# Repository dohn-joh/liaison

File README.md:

# Liaison
`Liaison` is a wireless 36-key split keyboard that leverages custom keycaps, splay, and tenting for ergonomics.

**Video showcase**:  
[Fit and layout](https://vimeo.com/1022366207)  
[Typing test](https://vimeo.com/1022366241)

***

# Components

## Case and Tenting Legs
[Here](case) you can find models for the case and magsafe tenting legs.  
Print 1 of each of the following:
* [top left](case/case_top_left.step)
* [top right](case/case_top_right.step)
* [bottom left](case/case_bottom_left.step)
* [bottom right](case/case_bottom_right.step)

[Tenting legs](case/magsafe_tenting_leg) (optional)  
[Dongle case](https://github.com/dohn-joh/dongle-zmk) (optional)

## Required Parts
|Part|Quantity|Link|
|-|:-:|-|
|Microcontroller: Xiao nRF52840|1|https://www.seeedstudio.com/Seeed-XIAO-BLE-nRF52840-p-5201.html|
|Battery: 301230 with molex pico ezmate connector|1|Select L0040. https://www.aliexpress.us/item/3256802674181210.html|
|Battery connector: molex pico ezmate 1x02|1|Select 2P. https://www.aliexpress.us/item/3256805726980487.html|
|Power button: 1208YD|1|https://www.aliexpress.us/item/3256801267126259.html|
|Reset button: SKHLLCA010|1|https://www.aliexpress.us/item/3256805176534062.html|
|M2 heatset inserts (OD:3.2, Height: 2-3mm)|8|https://www.aliexpress.us/item/3256804856964661.html|
|Switches|36|Your choice of choc v1 or v2. Recommended: Lofree ghost, swap springs|
|Kailh Choc PG1350 Hot Swap Sockets|36|https://www.aliexpress.us/item/3256803687338432.html|
|Silicone sheet for feet|1|https://www.amazon.com/dp/B09NW63JLC|
|Keycaps|36|Your choice. Recommended: [low profile DES](https://github.com/dohn-joh/PseudoMakeMeKeyCapProfiles) + [lever keycaps](https://github.com/dohn-joh/keycaps)|

> [!NOTE]
> Keycap dimensions must be ≤17.85mm wide and ≤18mm deep. All standard choc keycaps will fit.

## Optional Parts for Tenting Legs and Magnetic USB
|Part|Quantity|Link|
|-|:-:|-|
|Magsafe puck: Vrig MG-01|2|https://www.aliexpress.us/item/3256804940825578.html|
|Magsafe plate|2|https://www.amazon.com/dp/B09B6XGTWL|
|1/4" thread screw ~9mm|2|There are cheaper sources out there, but here is a link: https://www.amazon.com/dp/B01MS60KSY|
|Magnetic USB connector/cable: Netdot Gen10|2|https://www.amazon.com/dp/B07MBD3FZD|

## Firmware
[Here](https://github.com/dohn-joh/liaison-zmk-module) you can find the liaison's ZMK module. The firmware is configured for dongle usage, however you may fork the repo if you prefer to not use a dongle.

# Build Guide

**1. Order the pcb and acquire the case**
* Download the [left](ergogen/output/pcbs/production/Left_v1.0.0.zip) and [right](ergogen/output/pcbs/production/Right_v1.0.0.zip) pcb zip files.
* Upload the zip files to your pcb manufacturer of choice, then place an order. I used jlcpcb.
* Acquire the case:
    * If you own a 3d printer: print the [case](README.md#case-and-tenting).
    * If you don't own a 3d printer: order the case prints using [these files](README.md#case-and-tenting).

**2. Order [parts](README.md#required-parts)**

**3. Flash and test the microcontrollers**
> [!IMPORTANT]
> **Flash your microcontrollers with firmware and test them before doing any soldering.** Once the microcontrollers are soldered, they will be nearly impossible to remove without the right tools.
* Flash the [firmware](https://github.com/dohn-joh/liaison-zmk-module).
* Test to make sure that the microcontrollers are working and not defective (defective units are rare, but it happens).

**4. Solder components to top face of pcb**
* Set your soldering iron to 350C.
* Solder the microcontrollers, diodes, [reset switch](https://github.com/GEIGEIGEIST/TOTEM/blob/main/docs/buildguide.md#reset-switches), power switch, and battery connector to the top face of the pcb.
* The battery connector can be tricky to solder. But once you get the hang of it, it's pretty easy. Here are some tips from Kim:
    > Apply flux on both the pcb pads and battery connector pins  
    Tin both corner pads with solder  
    Solder connector to the first corner by applying heat to the corner metal pin from above  
    Then do the same for the second corner  
    Apply more flux to connector pins and PCB pads  
    Apply solder to underside of soldering tip  
    Drag iron from side to side over the contacts until they are soldered. The solder will just jump to where it needs to go  
    Make sure to clean the flux thoroughly
* The power button needs to face downward. Trim the power switch legs to size before installing. Secure the power switch in place with kapton tape after soldering.

**5. Check your work**
* This step is optional, but I like to check my work before moving on to soldering the other side of the pcb.
* Make sure all diodes are oriented correctly. All lines or arrows should be pointing left.
* Set your multimeter to continuity mode.
* Check connections and look for bridging.
* Fix any solder joints as needed.

**6. Solder components to bottom face of pcb**
> [!IMPORTANT]
> Hotswap socket orientation matters. The sockets must align with the silkscreen or the bottom case will not fit.
* Solder the hotswap sockets to the bottom face of the pcb.
* Optional: check your work with a multimeter.

**7. Battery installation**
* Plug the battery into the connector.
* Use kapton tape to secure the battery within the silkscreen outline.

**8. Case assembly**
* With your soldering iron set to 300C, push heatset inserts into the 4 holes on the top case.
* Insert the pcb.
* Attach the bottom case and secure it in place with the M2 screws.
    * If the bottom case doesn't sit flush in the area around the reset switch, then you may need to trim the reset switch legs.
* Cut silicone sheet to size and adhere to the corners of the bottom case.
* Insert the switches and keycaps.

**9. (Optional) Tenting assembly**
* Screw the magsafe pucks onto the tenting legs.
* Adhere magsafe plate to bottom case.
* Cut silicone sheet to size and adhere to bottom of tenting legs.

***

# Photos

***

## Thanks
These people and many more helped make this keyboard possible. Yall are legends.
```
MrZealot
Pseudoku
petejohanson
caksoylar(bravekarma)
jcmkk3
ceoloide
infused-kim
Flatfootfox
sadekbaroudi
zzeneg
joelspadin
wolfwood
claussen
Geist
rmwphd(atinyzubat)
fish
Araxia
honorless
elkepenin
reeves
```

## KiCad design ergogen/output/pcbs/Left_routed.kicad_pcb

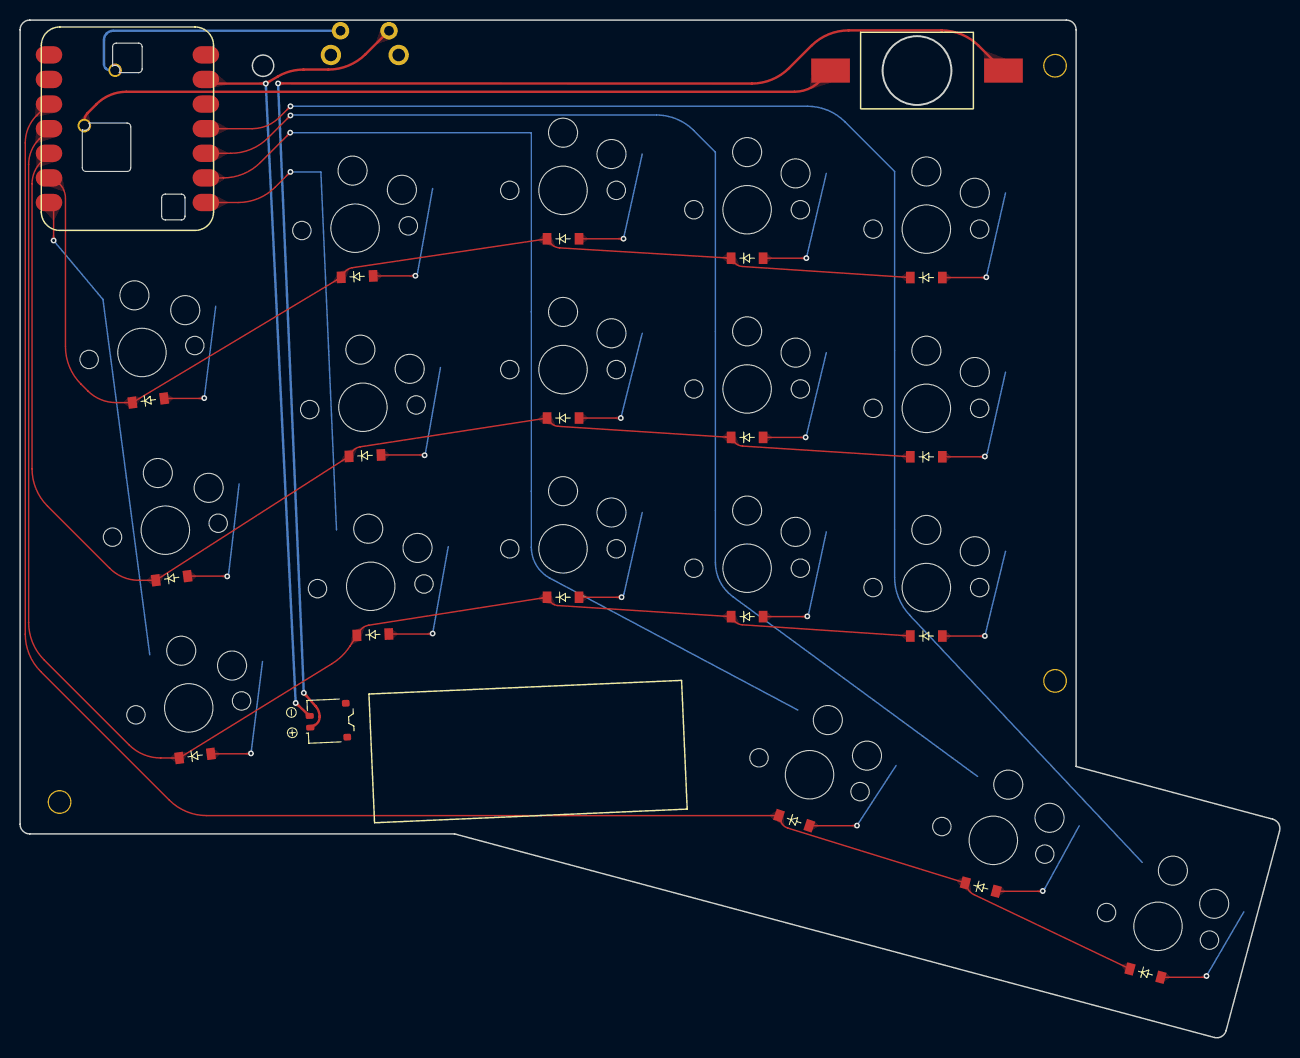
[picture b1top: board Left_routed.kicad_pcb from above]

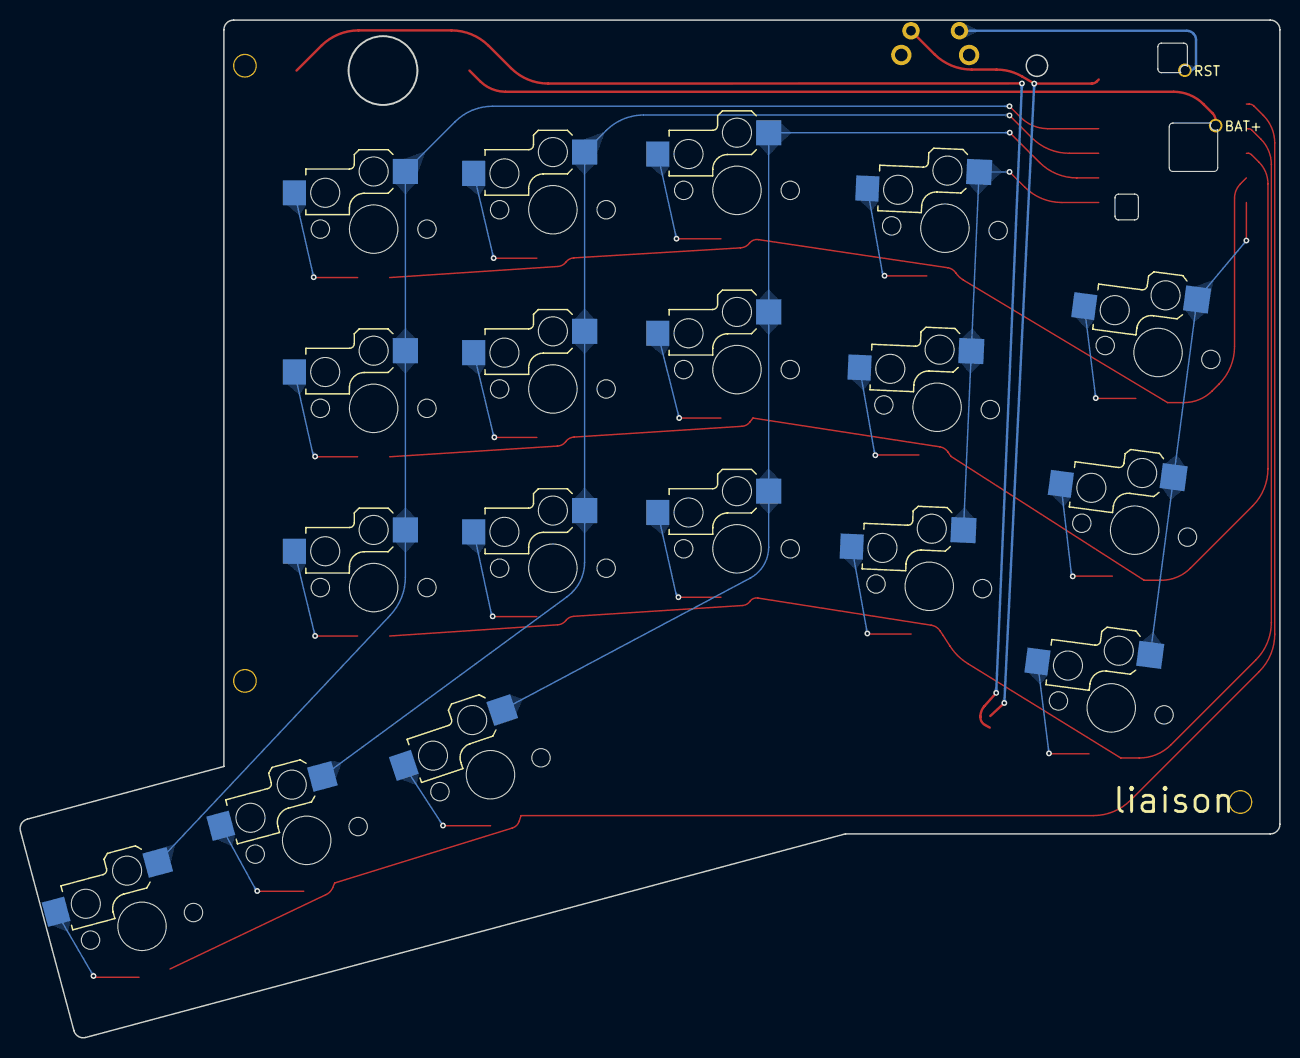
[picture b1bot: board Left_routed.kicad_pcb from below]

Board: 2 copper layers, 130.0 x 105.0 mm, 44 parts (18 on the bottom side), 31 nets.

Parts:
CONN1: conn_molex_pico_ezmate_1x02
D1, D2, D3, D4, D5, D6, D7, D8, D9, D10, D11, D12, D13, D14, D15, D16, D17, D18: ComboDiode
H1, H2, H3: mounting_hole
ICON1: icon_bat
MCU1: xiao_smd_xl_cutout_minimal
S1, S2, S3, S4, S5, S6, S7, S8, S9, S10, S11, S12, S13, S14, S15, S16, S17, S18: switch_choc_v1_v2
S19: SKHLLCA010
SW1: 1208YD

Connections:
BAT: MCU1.19, SW1.1
BAT_CONN: CONN1.1, SW1.2
C0: MCU1.7, S1.1, S2.1, S3.1
C1: MCU1.8, S4.1, S5.1, S6.1
C2: MCU1.9, S7.1, S8.1, S9.1, S16.1
C3: MCU1.10, S10.1, S11.1, S12.1, S17.1
C4: MCU1.11, S13.1, S14.1, S15.1, S18.1
GND: CONN1.2, MCU1.13, S19.2
R0: D3.1, D6.1, D9.1, D12.1, D15.1, MCU1.6
R1: D2.1, D5.1, D8.1, D11.1, D14.1, MCU1.5
R2: D1.1, D4.1, D7.1, D10.1, D13.1, MCU1.4
R3: D16.1, D17.1, D18.1, MCU1.3
RST: MCU1.17, S19.1
base_cluster: D17.2, S17.2
extension_cluster: D18.2, S18.2
flexion_cluster: D16.2, S16.2
index_bottom: D10.2, S10.2
index_home: D11.2, S11.2
index_top: D12.2, S12.2
inner_bottom: D13.2, S13.2
inner_home: D14.2, S14.2
inner_top: D15.2, S15.2
middle_bottom: D7.2, S7.2
middle_home: D8.2, S8.2
middle_top: D9.2, S9.2
pinky_bottom: D1.2, S1.2
pinky_home: D2.2, S2.2
pinky_top: D3.2, S3.2
ring_bottom: D4.2, S4.2
ring_home: D5.2, S5.2
ring_top: D6.2, S6.2

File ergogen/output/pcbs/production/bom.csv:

Designator,Footprint,Quantity,Value,LCSC Part #
CONN1,conn_molex_pico_ezmate_1x02,1,,
"D1, D10, D11, D12, D13, D14, D15, D16, D17, D18, D2, D3, D4, D5, D6, D7, D8, D9",ComboDiode,18,,
"H1, H2, H3",mounting_hole,3,,
MCU1,xiao_smd_xl_cutout_minimal,1,,
S19,SKHLLCA010,1,SKHLLCA010,
SW1,1208YD,1,,

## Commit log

2024-09-30 update sw cut
2024-10-09 fix xiao footprint
2024-10-13 update config
2024-10-23 add battery outlines to pcb
2024-10-25 update key_walls
2024-11-09 update case files
2024-11-13 update readme and photos
2024-11-15 add slicer settings
